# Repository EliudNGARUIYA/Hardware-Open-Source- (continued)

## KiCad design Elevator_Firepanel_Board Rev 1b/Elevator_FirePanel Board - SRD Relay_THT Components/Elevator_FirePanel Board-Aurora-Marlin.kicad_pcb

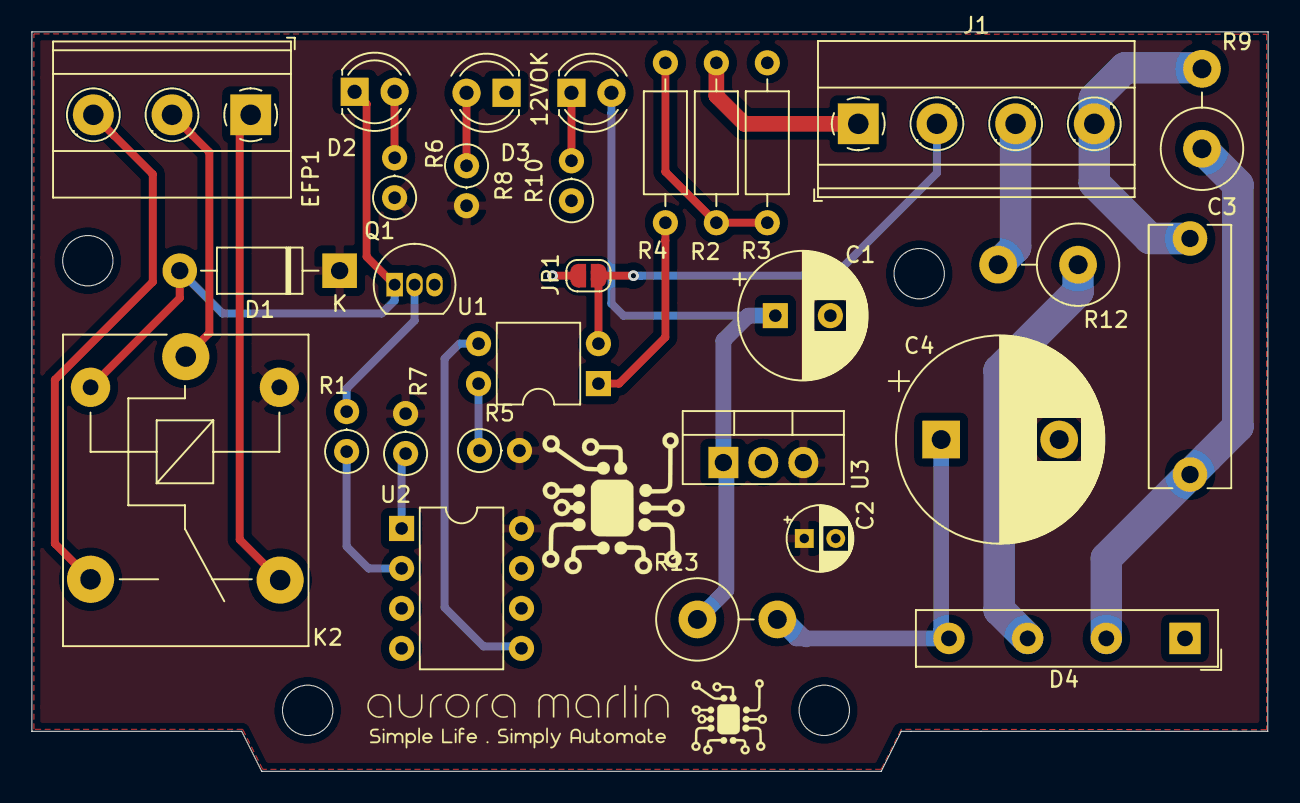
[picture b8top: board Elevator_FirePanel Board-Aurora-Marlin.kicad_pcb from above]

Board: 2 copper layers, 78.6 x 47.0 mm, 29 parts (0 on the bottom side), 24 nets.

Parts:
12VOK: Blue; LED_D4.0mm
C1: 100uF 35V; CP_Radial_D8.0mm_P3.50mm
C2: 10uF 35V; CP_Radial_D4.0mm_P2.00mm
C3: 474K 400V; C_Rect_L16.5mm_W5.0mm_P15.00mm_MKT
C4: 1000uF 50V; CP_Radial_D13.0mm_P7.50mm
D1: 1N4001; D_DO-41_SOD81_P10.16mm_Horizontal
D2: Red; LED_D4.0mm
D3: Green; LED_D4.0mm
D4: D_Bridge_-AA+; Diode_Bridge_19.0x3.5x10.0mm_P5.0mm
EFP1: Output; TerminalBlock_Phoenix_MKDS-1,5-3_1x03_P5.00mm_Horizontal
J1: Inputs; TerminalBlock_Phoenix_MKDS-1,5-4_1x04_P5.00mm_Horizontal
JP1: GROUND; SolderJumper-2_P1.3mm_Open_RoundedPad1.0x1.5mm
K2: SANYOU_SRD_Form_C; Relay_SPDT_SANYOU_SRD_Series_Form_C
Q1: BC547; TO-92_Inline
R1, R7: 10K; R_Axial_DIN0207_L6.3mm_D2.5mm_P2.54mm_Vertical
R2: 2K 1/2W; R_Axial_DIN0207_L6.3mm_D2.5mm_P10.16mm_Horizontal
R3: 1K 1/2W; R_Axial_DIN0207_L6.3mm_D2.5mm_P10.16mm_Horizontal
R4: 10K 1/2W; R_Axial_DIN0207_L6.3mm_D2.5mm_P10.16mm_Horizontal
R5: 4.7K; R_Axial_DIN0207_L6.3mm_D2.5mm_P2.54mm_Vertical
R6, R8, R10: 330; R_Axial_DIN0207_L6.3mm_D2.5mm_P2.54mm_Vertical
R9: 470K 1W; R_Axial_DIN0516_L15.5mm_D5.0mm_P5.08mm_Vertical
R12, R13: 100R 1W; R_Axial_DIN0516_L15.5mm_D5.0mm_P5.08mm_Vertical
U1: PC817; DIP-4_W7.62mm
U2: ATtiny13-20PU; DIP-8_W7.62mm
U3: LM7805_TO220; TO-220-3_Vertical

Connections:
+5V: C2.1, D1.1, K2.5, R5.2, R6.1, R7.2, R8.2, U2.8, U3.3
/DC+: 12VOK.2, C1.1, R13.1, U3.1
/Relay: R1.1, U2.2
ACL: C3.2, J1.4, R9.2
ACN: J1.3, R12.2
FN: J1.2, JP1.1, U1.2
FP: J1.1, R2.2
GND: C1.2, C2.2, C4.2, D3.1, D4.1, JP1.2, Q1.3, R3.1, R10.1, U2.4, U3.2
MOSI: U1.3, U2.5
unnamed: 12VOK.1, R10.2
unnamed: C3.1, D4.2, R9.1
unnamed: C4.1, D4.4, R13.2
unnamed: D1.2, D2.1, K2.2, Q1.1
unnamed: D2.2, R6.2
unnamed: D3.2, R8.1
unnamed: D4.3, R12.1
unnamed: EFP1.1, K2.4
unnamed: EFP1.2, K2.1
unnamed: EFP1.3, K2.3
unnamed: Q1.2, R1.2
unnamed: R2.1, R3.2, R4.2
unnamed: R4.1, U1.1
unnamed: R5.1, U1.4
Reset: R7.1, U2.1

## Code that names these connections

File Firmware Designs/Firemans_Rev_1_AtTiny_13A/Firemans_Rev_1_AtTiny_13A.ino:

/*
 * Firemans.cpp
 *
 * Created: 19/08/2019 20:10:57
 * Author : Aurora Marlin
 * 
 * Rev 1.0
 * PB0 --> Opto   (INPUT)
 * PB3 --> Relay (OUTPUT)
 * PB4 --> R_LED (OUTPUT)
 * 
 */ 

#define OPTO 0
#define RELAY 3
#define R_LED 4

int optoStatus = 0;
int lastState = 0;

void setup() {
  // initialize digital Pin 3 of ATtiny 13(defined in hardware as 4) as an output.
  pinMode(OPTO, INPUT);                  //PBO
  pinMode(RELAY, OUTPUT);                 //PB3
  pinMode(R_LED, OUTPUT);                 //PB4

  digitalWrite(RELAY, LOW);               //Initialize IO
  digitalWrite(R_LED, LOW);
  delay(800);
}
// the loop function runs over and over again forever
void loop() {
  optoStatus = digitalRead(OPTO);

  if(optoStatus == 1 && lastState == 0)
  {
    delay(30000);                           //Wait for 30 seconds before activating firemans switch
    digitalWrite(RELAY, HIGH);
    digitalWrite(R_LED, HIGH);

    lastState = 1;
  }
  else if(optoStatus == 0 && lastState == 1)
  {
    delay(5000);                           //Wait 30 seconds before returning to normal
    digitalWrite(RELAY, LOW);
    digitalWrite(R_LED, LOW);

    lastState = 0;
  }
  else if(optoStatus == 0 && lastState == 0)
  {
    //Do Nothing
  }
  else if (optoStatus == 1 && lastState == 1)
  {
    //Do Nothing
  }
}
